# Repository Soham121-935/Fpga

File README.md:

# SV-16 Rev B — 16-Bit Microcontroller on a Lattice ECP5

SV-16 is a complete 16-bit microcontroller system in synthesizable
SystemVerilog for the **Lattice ECP5 `LFE5U-12F-6TG144C`**. It is not just a
CPU: it boots from SPI flash by itself, runs applications out of on-chip SRAM,
and can be reprogrammed over a plain serial port.

```
        ┌──────────────────────── LFE5U-12F-6TG144C ─────────────────────────┐
 25 MHz │  boot ROM (monitor)          SRAM 32 KB          MMIO 16 blocks    │
 ──────►│  ┌────────────┐   ┌──────────────────────┐  ┌──────────────────┐   │
        │  │ SV-16 CPU  │──►│ bus interconnect     │─►│ GPIO A/B, timer, │   │
 reset ─►│  │ 8 regs,    │   │ held req / qual ack  │  │ PWM+fault, UART, │   │
        │  │ 16-bit ALU │   │ held grant, 2 masters│  │ SPI, flash ctrl, │   │
        │  └────────────┘   └──────────────────────┘  │ IRQ, boot, system│   │
        │                                  watchdog ──►│  WDT, GPIO, SPI  │   │
        │      ▲ boot loader (hardware) ─────────────────────────────────►   │
        └──────┼───────────────────────────────────────────────┬──────────┘
               │  streams + CRC-checks the image from flash    │ 4 SPI pins
        ┌──────┴──────────────────────────┐            ┌───────┴─────────┐
        │  SPI NOR flash — the firmware   │            │ UART console /  │
        │  (survives power cycles)        │            │ upload 115200   │
        └─────────────────────────────────┘            └─────────────────┘
```

## Quick start

```sh
source scripts/sv16_venv.sh    # fetches Verilator + Yosys + nextpnr + ecppack
make test                      # lint + 18 simulation suites (473 checks)
make bitstream                 # -> build/sv16_top.bit (boot ROM baked in)
make prog                      # openFPGALoader over JTAG
make release                   # verify all four artifacts + hashes (run before programming)
make app                       # build the example application image
make upload PORT=/dev/ttyUSB0  # erase + upload + verify over UART
make upload-slot SLOT=1        # field update: install into the inactive slot
make mon-boot && make commit   # boot it (trial starts), then commit it
```

A fresh board comes up as a monitor on the serial port at **115200 8-N-1**:

```
SV-16 monitor v1
> ?
  C<addr4><len4><crc4>  program flash (hex payload follows)
  R<addr4><len4>        read flash
  E<addr4>              erase 4 KB sector
  V<addr4>              CRC16 of the image at addr
  B                     verify and boot the image at 0
  ?                     this help
+
```

## What it can do

* **16-bit CPU** — 8 general-purpose registers, `LDI/JMP/CALL` 2-word forms,
  ALU with multiply/divide/shift, Z/C/N/V flags, interrupt-enable flag, trap on
  illegal opcodes ([ISA.md](docs/ISA.md)).
* **32 KB SRAM, 4 KB boot ROM, 16 MMIO blocks** — a documented map with no
  decode holes that can hang the bus ([MEMORY_MAP.md](docs/MEMORY_MAP.md)).
* **Peripherals** — two 16-bit GPIO ports with atomic set/clear, timer, PWM with
  a hardware motor-fault input, UART with FIFOs, SPI master, a full SPI-NOR flash
  controller (read/program/erase/CRC), interrupt controller with priority and an
  8-entry vector table, and a **windowed, key-protected watchdog** that restarts
  the SoC if the application hangs ([PERIPHERALS.md](docs/PERIPHERALS.md#watchdog-0xf080)).
* **Real boot flow** — power-on → hardware loader validates and copies the flash
  image → CPU released at the application's entry point with the application's
  stack pointer; any failure falls back to the resident monitor
  ([BOOT_AND_PROGRAMMING.md](docs/BOOT_AND_PROGRAMMING.md)).
* **Field updates over UART** — CRC-checked images, per-byte acknowledgement,
  hex protocol a human can type, or `make upload` with `scripts/sv16_mon.py`.
* **Recoverable by design** — the monitor and the loader are in the FPGA
  configuration, so a broken application cannot brick the board; reset causes,
  fault addresses and a CPU state snapshot are all readable registers. A hung
  application is restarted by the watchdog, which the application cannot disarm
  and which re-arms itself after every bite.

## Build targets

| Command | Result |
| :--- | :--- |
| `make test` | lint + all eighteen Verilator suites (473 checks) |
| `make pcb` | the whole board starter kit: KiCad schematic and board file, six bitmaps, BOM/CPL, `FAB_NOTES.md`, `PCB_CONNECTIONS.md` |
| `make pcb-check` | parse the generated schematic and board back and re-verify them (nets, pads, DRC-lite, placement) |
| `make app` | build the example application image |
| `make bitstream` | `build/sv16_top.bit` for the LFE5U-12F-6TG144C, timing PASS at 25 MHz |
| `make synth` | Yosys only (fast synthesizability check) |
| `make prog` | program the FPGA over JTAG |
| `make release` | build the bitstream and the A/B image, then verify every artifact (ROM matches its source, timing, device budget, image CRCs, slot record) and write `build/release/` with hashes and the programming sequence |
| `make upload PORT=...` | program the *firmware* over the serial port |
| `make upload-slot SLOT=1` | field update into the inactive A/B slot (ADR-019) |
| `make commit` | commit a trial image (monitor `K`) |
| `make iss` | instruction-set simulator on the legacy ROM image |

Clocking: `CLKSRC=osc` (default) runs the SoC straight from the 25 MHz oscillator
— no PLL, no fabric divider — with ~75 % timing margin (measured Fmax 43.7 MHz);
`make bitstream CLKSRC=pll PLLMHZ=37.5` builds a **37.5 MHz** version from the
on-chip PLL (ADR-021), and `CLKDIV=2` halves whichever source is selected. The
UART divisor is derived from the built clock automatically (217 at 25 MHz, 326 at
37.5 MHz), so the console is always 115200 and firmware does not care.

## Repository layout

```text
BOARD.md/.pdf    PCB blueprint: components, specs, power tree, connection diagram
TEAM_PLAN.md/.pdf 4-person build plan: roles, phases, work packages, gates, budget, risks
hardware/       KiCad schematic (sv16_board.kicad_sch) + board base (footprints + netlist
                + rail pours + escape vias, ready to route)
                + six board bitmaps (top, bottom, net map, power map, connection sheets, schematic)
                + BOM.csv, JLCPCB_BOM.csv, JLCPCB_CPL.csv, FAB_NOTES.md (ordering and assembly)
                + cart/ (the parts you actually bought, reconciled against footprints)
PCB_CONNECTIONS.md/.pdf  the wiring: every pad, every net, every connector pinout, drawn
KICAD_TUTORIAL.md/.pdf  the click-by-click guide to finishing that board in KiCad
board/           device pin database + generated 144-pin net table (BOARD.md appendix)
docs/            operator manual, memory map, peripherals, flow, verification, ADRs
rtl/             26 SystemVerilog files: CPU, bus, memory, peripherals, PLL, SoC top
simulation/      Verilator testbenches (unit + regression) and the SPI flash model
firmware/        monitor assembler source, examples, drivers header, image packer
constraints/     ecp5_144tqfp.lpf — verified pin map for the TQFP-144 part
scripts/         assembler, image packer, RTL lint, TB runner, host programmer, toolchain
build/           generated: ROM image, firmware images, netlist, bitstream (untracked)
```

## Status, honestly

| | |
| :--- | :--- |
| Simulation | 473 checks, 0 failures across 18 suites (CPU/ISA, control instructions, interrupt latency, ALU/divider, RAM, timer, PWM, GPIO, UART, watchdog, flash controller, boot loader, A/B slots, PLL clock, monitor) |
| Synthesis / P&R | places, routes, packs for the target part; 77 % of the datasheet's LUT budget, 56 % of its block RAM (checked by the build, ADR-025) |
| Timing | 44.70 MHz Fmax measured at 25 MHz (~79 % margin); 45.45 MHz at `CLKSRC=pll PLLMHZ=37.5` (~21 % margin) |
| Silicon | **never run on hardware** — simulation and static timing only |

What is still missing for a production-grade MCU (JTAG debug, image signing,
a C toolchain, silicon bring-up) is
listed with reasoning in
**[docs/MCU_READINESS.md](docs/MCU_READINESS.md)** — including an explicit
MCU-like vs. FPGA-soft-core comparison.

## Documentation

| Document | Contents |
| :--- | :--- |
| [PCB_CONNECTIONS.pdf](PCB_CONNECTIONS.pdf) | **start here if you are the one wiring or routing it**: every pad of every part and what it connects to, connector pinouts, the power tree, the six connection sheets drawn, what the generator already connected, and the twelve checks before routing (source: [PCB_CONNECTIONS.md](PCB_CONNECTIONS.md), rebuild with `make pcb-connections-pdf`) |
| [KICAD_TUTORIAL.pdf](KICAD_TUTORIAL.pdf) | **start here if you are the one routing the board**: opening the project, updating the footprints, the design rules, filling and splitting the planes, the routing order with exact widths, DRC, gerbers, ordering, assembly and first power-up (source: [KICAD_TUTORIAL.md](KICAD_TUTORIAL.md), rebuild with `make tutorial-pdf`) |
| [TEAM_PLAN.pdf](TEAM_PLAN.pdf) | how to build this with four people: roles, five phases, gates, 16 work packages, interfaces to freeze, budget, risks (source: [TEAM_PLAN.md](TEAM_PLAN.md), rebuild with `make plan-pdf`) |
| [BOARD.pdf](BOARD.pdf) | the same blueprint typeset for printing / review (source: [BOARD.md](BOARD.md), rebuild with `make board-pdf`) |
| [BOARD.md](BOARD.md) | PCB blueprint — BOM with part numbers, power tree, pin map, connection circuit diagram, bring-up plan, open items |
| [board/TQFP144_PINOUT.md](board/TQFP144_PINOUT.md) | generated 144-pin device table: pad, bank, rail, design signal, board net |
| [BOOT_AND_PROGRAMMING.md](docs/BOOT_AND_PROGRAMMING.md) | boot flow, monitor protocol, image format, host tools, recovery |
| [MCU_READINESS.md](docs/MCU_READINESS.md) | what is MCU-like, what is still soft-core, gap list |
| [SYNTHESIS_AND_DEPLOYMENT.md](docs/SYNTHESIS_AND_DEPLOYMENT.md) | toolchain, build targets, utilisation, timing, pin map, programming |
| [MEMORY_MAP.md](docs/MEMORY_MAP.md) | address map, MMIO blocks, vector table |
| [PERIPHERALS.md](docs/PERIPHERALS.md) | register reference for every block |
| [BUS_ARCHITECTURE.md](docs/BUS_ARCHITECTURE.md) | protocol, arbitration, timing, adding a peripheral |
| [VERIFICATION.md](docs/VERIFICATION.md) | what is tested, what is not, bugs found |
| [RESET_AND_CLOCK.md](docs/RESET_AND_CLOCK.md) | clocking, reset sources, startup FSM |
| [ISA.md](docs/ISA.md) | instruction set, encodings, Rev B notes |
| [ARCHITECTURE_DECISIONS.md](docs/ARCHITECTURE_DECISIONS.md) | ADR-001..005 (Rev A), ADR-012..016 (Rev B) |

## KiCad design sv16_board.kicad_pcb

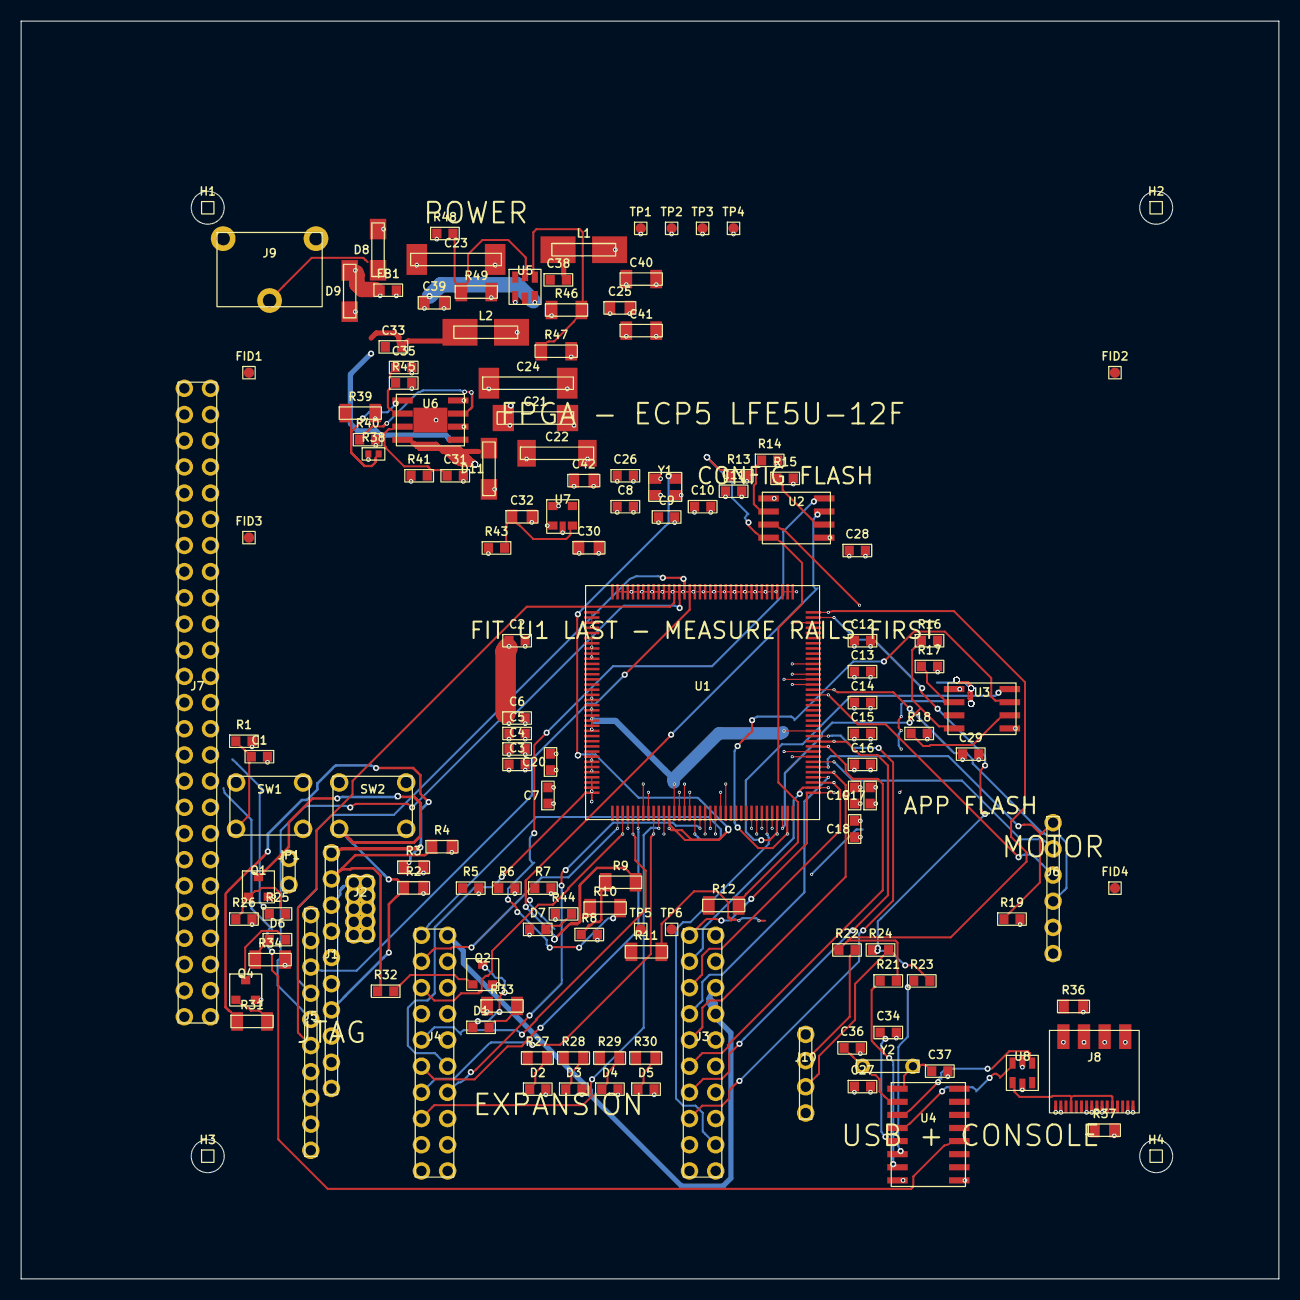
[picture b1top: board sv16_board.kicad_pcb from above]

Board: 4 copper layers, 122.0 x 122.0 mm, 141 parts (0 on the bottom side), 118 nets.

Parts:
C1, C2, C3, C4, C5, C6, C7, C8, C9, C10, C11, C12, C13, C14, C15, C16, C17, C18, C19, C20, C26, C27, C28, C29, C33, C34, C35, C36, C37, C38: 100nF; C_0603_1608Metric
C21: 100uF 25V tant; CP_EIA-7343-31_Kemet-D
C22: 22uF 63V; CP_Elec_6.3x5.4
C23: 470uF 25V; CP_Elec_8x10.5
C24: 220uF 16V; CP_Elec_8x10.5
C25, C30, C39, C42: 10uF; C_0805_2012Metric
C31: 470nF; C_0603_1608Metric
C32: 470nF; C_0805_2012Metric
C40, C41: 22uF; C_1206_3216Metric
D1, D2, D3, D4, D5: LED green; LED_0603_1608Metric
D6, D7: LED red; LED_0603_1608Metric
D8, D9, D11: SS34; D_SMA
FB1: 600R @100MHz; L_0603_1608Metric
FID1: FID1; Fiducial_1mm_Mask2mm
FID2: FID2; Fiducial_1mm_Mask2mm
FID3: FID3; Fiducial_1mm_Mask2mm
FID4: FID4; Fiducial_1mm_Mask2mm
H1: H1; MountingHole_3.2mm_M3
H2: H2; MountingHole_3.2mm_M3
H3: H3; MountingHole_3.2mm_M3
H4: H4; MountingHole_3.2mm_M3
J1: JTAG; PinHeader_1x10_P2.54mm_Vertical
J2: JTAG-1.27; PinHeader_2x05_P1.27mm_Vertical
J3: EXP-A; PinHeader_2x10_P2.54mm_Vertical
J4: EXP-B; PinHeader_2x10_P2.54mm_Vertical
J5: EXP-C; PinHeader_1x10_P2.54mm_Vertical
J6: MOTOR; PinHeader_1x06_P2.54mm_Vertical
J7: SPARE (not fitted); PinHeader_2x25_P2.54mm_Vertical
J8: USB-C; USB_C_Receptacle_HRO_TYPE-C-31-M-12
J9: 7-12 V; BarrelJack_CUI_PJ-102AH_Horizontal
J10: CONSOLE; PinHeader_1x04_P2.54mm_Vertical
JP1: DTR ENABLE; PinHeader_1x02_P2.54mm_Vertical
L1, L2: 10 uH; L_Sunlord_MWSA0518_5.4x5.2mm
Q1: 2N7002; SOT-23
Q2: BC817; SOT-23
Q4: BC807; SOT-23
R1: R1; R_0603_1608Metric
R2: R2; R_0805_2012Metric
R3: R3; R_0805_2012Metric
R4: R4; R_0805_2012Metric
R5: R5; R_0603_1608Metric
R6: R6; R_0603_1608Metric
R7: R7; R_0603_1608Metric
R8: R8; R_0603_1608Metric
R9: R9; R_1206_3216Metric
R10: R10; R_1206_3216Metric
R11: R11; R_1206_3216Metric
R12: R12; R_1206_3216Metric
R13: R13; R_0603_1608Metric
R14: R14; R_0603_1608Metric
R15: R15; R_0603_1608Metric
R16: R16; R_0603_1608Metric
R17: R17; R_0603_1608Metric
R18: R18; R_0603_1608Metric
R19: R19; R_0603_1608Metric
R21: R21; R_0603_1608Metric
R22: R22; R_0603_1608Metric
R23: R23; R_0603_1608Metric
R24: R24; R_0603_1608Metric
R25: R25; R_0603_1608Metric
R26: R26; R_0603_1608Metric
R27: R27; R_0805_2012Metric
R28: R28; R_0805_2012Metric
R29: R29; R_0805_2012Metric
R30: R30; R_0805_2012Metric
R31: R31; R_1206_3216Metric
R32: R32; R_0603_1608Metric
R33: R33; R_1206_3216Metric
R34: R34; R_1206_3216Metric
R36, R37: 5.1k; R_0805_2012Metric
R38: 12.4k; R_0402_1005Metric
R39, R46, R49: 33k; R_1206_3216Metric
R40, R41, R43, R48: 100k; R_0603_1608Metric
R44: R44; R_0603_1608Metric
R45: 10k; R_0603_1608Metric
R47: 10k; R_1206_3216Metric
SW1: RESET; SW_PUSH_6mm
SW2: RECONFIG; SW_PUSH_6mm
TP1: 3V3; TestPoint_Pad_D1.0mm
TP2: 2V5; TestPoint_Pad_D1.0mm
TP3: 1V1; TestPoint_Pad_D1.0mm
TP4: GND; TestPoint_Pad_D1.0mm
TP5: DONE; TestPoint_Pad_D1.0mm
TP6: INITN; TestPoint_Pad_D1.0mm
U1: LFE5U-12F-6TG144C; LQFP-144_20x20mm_P0.5mm
U2, U3: W25Q64JVSSIQ; SOIC-8_5.23x5.23mm_P1.27mm
U4: CH340G; SOIC-16_3.9x9.9mm_P1.27mm
U5: AP62300TWU-7; SOT-23-6
U6: MP1584EN; SOIC-8-1EP_3.9x4.9mm_P1.27mm_EP2.41x3.3mm
U7: LP5907MFX-2.5; SOT-23-5
U8: USBLC6-2SC6; SOT-23-6
Y1: 25 MHz ACTIVE XO (4-pin); Oscillator_SMD_Abracon_ASE-4Pin_3.2x2.5mm
Y2: 12 MHz (CH340G clock); Crystal_HC49-4H_Vertical

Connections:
1V1: C2.1, C3.1, C4.1, C5.1, C6.1, C7.1, C21.1, L2.2, R38.1, TP3.1, U1.20, U1.29, U1.38, U1.66, U1.83, U1.130
2V5: C8.1, C9.1, C10.1, C11.1, C22.1, C42.1, TP2.1, U1.17, U1.53, U1.96, U1.132, U7.5
3V3: C12.1, C13.1, C14.1, C15.1, C16.1, C17.1, C18.1, C19.1, C20.1, C24.1, C25.1, C26.1, C27.1, C28.1, C29.1, C30.1, C40.1, C41.1, D2.2, D3.2, D4.2, D5.2, J1.1, J2.1, J3.1, J4.1, J5.10, J10.1, L1.2, Q4.2, R1.2, R2.2, R3.2, R4.2, R5.2, R8.2, R13.2, R14.2, R15.2, R16.2, R17.2, R18.2, R19.2, R33.1, R43.1, R44.1, R46.1, TP1.1, U1.9, U1.16, U1.36, U1.43, U1.70, U1.86, U1.100, U1.122, U1.137, U2.8, U3.8, U4.16, U7.1, Y1.1, Y1.4
5V_USB: J3.17, J3.18, J4.20
A0: J5.1, U1.45
A1: J5.2, R11.1, U1.46
A2: J5.3, R10.1, U1.47
A3: J5.4, U1.48
A4: J5.5, R12.1, U1.49
A5: J5.6, U1.50
A6: J5.7, U1.51
A7: J5.8, U1.52
A8: J3.3, U1.97
A9: J3.4, U1.98
A10: J3.5, U1.99
A11: J3.6, U1.104
A12: J3.7, U1.105
A13: J3.8, U1.106
A14: J3.9, U1.107
A15: J3.10, U1.108
B0: J4.3, U1.135
B1: J4.4, U1.136
B2: J4.5, U1.139
B3: J4.6, U1.140
B4: J4.7, U1.141
B5: J4.8, U1.142
B6: J4.9, U1.143
B7: J4.10, U1.128
B8: J4.11, U1.124
B9: J4.12, U1.125
B10: J4.13, U1.126
B11: J4.14, U1.127
B12: J4.15, U1.1
B13: J4.16, U1.2
B14: J4.17, U1.3
B15: J4.18, U1.4
CC1: J8.A5, R36.1
CC2: J8.B5, R37.1
CCLK: R8.1, R9.1, U1.54
CFG_0: R6.1, U1.62
CFG_1: R5.1, U1.59
CFG_2: R7.1, U1.58
D1_A: D1.2, R33.2
D6_K: D6.1, R34.1
D7_A: D7.2, R44.2
DONE: J1.9, R4.1, R32.1, TP5.1, U1.56
DTR_F: JP1.2, R25.1
FB_1V1: R38.2, R39.1, U6.4
GND: C1.2, C2.2, C3.2, C4.2, C5.2, C6.2, C7.2, C8.2, C9.2, C10.2, C11.2, C12.2, C13.2, C14.2, C15.2, C16.2, C17.2, C18.2, C19.2, C20.2, C21.2, C22.2, C23.2, C24.2, C25.2, C26.2, C27.2, C28.2, C29.2, C30.2, C31.2, C32.2, C34.2, C35.2, C36.2, C37.2, C39.2, C40.2, C41.2, C42.2, D7.1, D11.2, J1.7, J2.6, J2.10, J3.2, J3.15, J3.16, J3.19, J3.20, J4.2, J4.19, J5.9, J6.2, J8.A1, J8.A12, J8.B1, J8.B12, J8.S1, J8.S2, J8.S3, J8.S4, J9.2, J10.4, Q1.2, Q2.2, R6.2, R7.2, R26.2, R34.2, R36.2, R37.2, R39.2, R40.2, R45.2, R47.2, R49.2, SW1.2, SW2.2, TP4.1, U1.8, U1.15, U1.21, U1.32, U1.42, U1.65, U1.75, U1.85, U1.87, U1.101, U1.123, U1.129, U1.131, U1.138, U2.4, U3.4, U4.1, U5.1, U6.5, U6.9, U7.2, U8.2, Y1.2
INITN: J1.10, R3.1, R31.1, TP6.1, U1.55
J9_VIN: D8.2, J9.1
J10_RX: J10.3, R22.2
J10_TX: J10.2, R24.2
PROGRAMN: J1.4, Q1.3, R2.1, SW2.1, U1.57
Q1_G: Q1.1, R25.2, R26.1
Q2_B: Q2.1, R32.2
Q2_C: D1.1, Q2.3
Q4_B: Q4.1, R31.2
Q4_C: D6.2, Q4.3
TCK: J1.8, J2.5, U1.63
TDI: J1.3, J2.3, U1.61
TDO: J1.2, J2.4, U1.60
TMS: J1.6, J2.2, U1.64
U2_CLK: R9.2, U2.6
U2_CS: R12.2, R13.1, U2.1
U2_DI: R10.2, U2.5
U2_DO: R11.2, U2.2
U2_HOLD: R15.1, U2.7
U2_WP: R14.1, U2.3
U3_HOLD: R18.1, U3.7
U3_WP: R17.1, U3.3
U4_DTR: JP1.1, U4.13
U4_RXD: R23.1, U4.3
U4_TXD: R21.1, U4.2
U4_V3: C34.1, U4.4
U5_BST: C38.1, U5.6
U5_EN: R48.2, R49.1, U5.5
U5_FB: R46.2, R47.1, U5.4
U5_SW: C38.2, L1.1, U5.2
U6_BST: C33.1, U6.8
U6_COMP: C35.1, R45.1, U6.3
U6_EN: C31.1, R41.2, U6.2
U6_FREQ: R40.1, U6.6
U6_SW: C33.2, D11.1, L2.1, U6.1
U7_EN: C32.1, R43.2, U7.3
USB_DN: J8.A7, J8.B7, U8.3
USB_DN_F: U4.6, U8.4
USB_DP: J8.A6, J8.B6, U8.1
USB_DP_F: U4.5, U8.6
USB_VBUS: D9.2, J8.A4, J8.A9, J8.B4, J8.B9, U8.5
VM_IN: C23.1, C39.1, FB1.2, J6.1, R41.1, R48.1, U5.3, U6.7
VM_IN_RAW: D8.1, D9.1, FB1.1
Y2_XI: C36.1, U4.7, Y2.1
Y2_XO: C37.1, U4.8, Y2.2
clk_25m: U1.133, Y1.3
ext_rst_n: C1.1, R1.1, SW1.1, U1.134
flash_cs_n: R16.1, U1.111, U3.1
flash_miso: U1.113, U3.2
flash_mosi: U1.112, U3.5
flash_sck: U1.110, U3.6
led0: R27.1, U1.39
led0_k: D2.1, R27.2
led1: R28.1, U1.40
led1_k: D3.1, R28.2
led2: R29.1, U1.41
led2_k: D4.1, R29.2
led3: R30.1, U1.44
led3_k: D5.1, R30.2
motor_dir1: J6.4, U1.89
motor_dir2: J6.5, U1.102
motor_fault_n: J6.6, R19.1, U1.103
pwm_out: J6.3, U1.88
spi0_cs_n: J3.11, U1.115
spi0_miso: J3.14, U1.117
spi0_mosi: J3.13, U1.116
spi0_sck: J3.12, U1.114
uart_rx: R21.2, R22.1, U1.73
uart_tx: R23.2, R24.1, U1.74

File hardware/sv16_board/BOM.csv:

Quantity,Value,Footprint,References,Part number,DNP,Notes
1,7-12 V,BarrelJack_CUI_PJ-102AH_Horizontal,J9,,,
1,100uF 25V tant,CP_EIA-7343-31_Kemet-D,C21,"100 uF 25 V tantalum, D case",,1V1 bulk; mind the polarity bar
1,22uF 63V,CP_Elec_6.3x5.4,C22,22 uF 63 V electrolytic,,D6.3 x L5.4 mm
1,220uF 16V,CP_Elec_8x10.5,C24,220 uF hybrid electrolytic,,D8 x L10.5 mm; hybrid polymer is better for ripple
1,470uF 25V,CP_Elec_8x10.5,C23,470 uF 25 V (35 V preferred),,the cart part is 16 V - on a 12 V rail that is only 1.33x derating
30,100nF,C_0603_1608Metric,C1 C2 C3 C4 C5 C6 C7 C8 C9 C10 C11 C12 C13 C14 C15 C16 C17 C18 C19 C20 C26 C27 C28 C29 C33 C34 C35 C36 C37 C38,,,
1,470nF,C_0603_1608Metric,C31,,,
4,10uF,C_0805_2012Metric,C25 C30 C39 C42,10 uF,,TO BUY - 3V3 bulk near the FPGA banks
1,470nF,C_0805_2012Metric,C32,,,
2,22uF,C_1206_3216Metric,C40 C41,22 uF X5R 25 V,,TO BUY - 3V3 output ceramic
1,12 MHz (CH340G clock),Crystal_HC49-4H_Vertical,Y2,12 MHz crystal,,"CH340G clock; CL 12-20 pF, choose C36/C37 to match"
3,SS34,D_SMA,D8 D9 D11,SS34,,SMA; input ORing
4,,Fiducial_1mm_Mask2mm,FID1 FID2 FID3 FID4,,,
5,LED green,LED_0603_1608Metric,D1 D2 D3 D4 D5,,,
1,LED red,LED_0603_1608Metric,D6,,yes,
1,LED red,LED_0603_1608Metric,D7,,,
1,LFE5U-12F-6TG144C,LQFP-144_20x20mm_P0.5mm,U1,LFE5U-12F-6TG144C,,no substitute; order a spare (BOARD.md 3.4)
1,600R @100MHz,L_0603_1608Metric,FB1,600 ohm @ 100 MHz ferrite,,"0603, >= 500 mA"
2,10 uH,L_Sunlord_MWSA0518_5.4x5.2mm,L1 L2,CD54 10 uH >= 1.5 A,,AP62300 3V3 inductor; the cart has 2 x 33 uH as spares
4,,MountingHole_3.2mm_M3,H1 H2 H3 H4,,,
1,25 MHz ACTIVE XO (4-pin),Oscillator_SMD_Abracon_ASE-4Pin_3.2x2.5mm,Y1,YIC OSC25M-3.3I/S3-25T,,"ACTIVE 25 MHz 3.3 V XO, 4-pin - a 2-pin crystal will not clock the FPGA"
1,DTR ENABLE,PinHeader_1x02_P2.54mm_Vertical,JP1,,,
1,CONSOLE,PinHeader_1x04_P2.54mm_Vertical,J10,,,
1,MOTOR,PinHeader_1x06_P2.54mm_Vertical,J6,,,
1,EXP-C,PinHeader_1x10_P2.54mm_Vertical,J5,,,
1,JTAG,PinHeader_1x10_P2.54mm_Vertical,J1,,,
1,JTAG-1.27,PinHeader_2x05_P1.27mm_Vertical,J2,,,
1,EXP-A,PinHeader_2x10_P2.54mm_Vertical,J3,,,
1,EXP-B,PinHeader_2x10_P2.54mm_Vertical,J4,,,
1,SPARE (not fitted),PinHeader_2x25_P2.54mm_Vertical,J7,,yes,
1,12.4k,R_0402_1005Metric,R38,,,
14,,R_0603_1608Metric,R1 R5 R6 R7 R8 R13 R14 R15 R16 R17 R18 R25 R26 R32,,,
3,0R,R_0603_1608Metric,R21 R23 R44,,,
2,0R (or not fitted),R_0603_1608Metric,R22 R24,,,
4,100k,R_0603_1608Metric,R40 R41 R43 R48,,,
2,10k,R_0603_1608Metric,R19 R45,,,
7,,R_0805_2012Metric,R2 R3 R4 R27 R28 R29 R30,,,
2,5.1k,R_0805_2012Metric,R36 R37,,,
7,,R_1206_3216Metric,R9 R10 R11 R12 R31 R33 R34,,,
1,10k,R_1206_3216Metric,R47,10 kohm 1 %,,TO BUY - AP62300 feedback bottom leg
3,33k,R_1206_3216Metric,R39 R46 R49,,,
1,CH340G,SOIC-16_3.9x9.9mm_P1.27mm,U4,CH340G,,SOP-16; needs Y2 12 MHz + C36/C37 (the C variant does not)
1,MP1584EN,SOIC-8-1EP_3.9x4.9mm_P1.27mm_EP2.41x3.3mm,U6,MP1584EN-LF-Z,,SOIC-8E; solder the exposed pad (thermal vias are placed)
2,W25Q64JVSSIQ,SOIC-8_5.23x5.23mm_P1.27mm,U2 U3,W25Q64JVSSIQ,,bitstream flash
1,2N7002,SOT-23,Q1,2N7002,,"SOT-23, PROGRAMN pull-down from DTR"
1,BC807,SOT-23,Q4,MMBT3906 (cart) / BC807,,INITN indicator
1,BC817,SOT-23,Q2,MMBT3904 (cart) / BC817,,DONE indicator
1,LP5907MFX-2.5,SOT-23-5,U7,LP5907MFX-2.5,,SOT-23-5; needs a low-ESR 10 uF on OUT (C42)
1,AP62300TWU-7,SOT-23-6,U5,AP62300TWU-7,,TSOT-26; EN is a 6 V pin - use the R48/R49 divider
1,USBLC6-2SC6,SOT-23-6,U8,USBLC6-2SC6,,"SOT-23-6, place at the connector"
1,RECONFIG,SW_PUSH_6mm,SW2,,,
1,RESET,SW_PUSH_6mm,SW1,,,
1,1V1,TestPoint_Pad_D1.0mm,TP3,,,
1,2V5,TestPoint_Pad_D1.0mm,TP2,,,
1,3V3,TestPoint_Pad_D1.0mm,TP1,,,
1,DONE,TestPoint_Pad_D1.0mm,TP5,,,
1,GND,TestPoint_Pad_D1.0mm,TP4,,,
1,INITN,TestPoint_Pad_D1.0mm,TP6,,,
1,USB-C,USB_C_Receptacle_HRO_TYPE-C-31-M-12,J8,,,

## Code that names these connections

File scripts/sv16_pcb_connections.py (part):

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    "VM_IN_RAW": "barrel / USB ORing node before FB1",
    "USB_VBUS": "5 V from the USB-C connector",
    "5V_USB": "VBUS only - J3/J4 pins 17/18/20, do not power the board here",
    "CCLK": "FPGA configuration clock (pin 54), R8 pull-up, R9 to U2",
    "U2_CLK": "U2 clock after the 100 ohm damping resistor",
    "MOSI": "FPGA configuration data out (pin 47)", "U2_DI": "U2 data in",
    "MISO": "FPGA configuration data in (pin 46)", "U2_DO": "U2 data out",
    "CSSPIN": "FPGA configuration chip select (pin 49)", "U2_CS": "U2 chip select",
    "U2_WP": "U2 write protect (pulled high)", "U2_HOLD": "U2 hold (pulled high)",
    "PROGRAMN": "configuration trigger, active low", "INITN": "SRAM clear / config error",
    "DONE": "configuration complete, high when running",
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    "DTR": "CH340G DTR# output", "DTR_F": "DTR after the JP1 jumper",
    "Q2_B": "Q2 base", "Q2_C": "Q2 collector", "DONE_LED": "D1 anode",
    "Q4_B": "Q4 base", "Q4_C": "Q4 collector", "INITN_LED": "D6 cathode side",
    "clk_25m": "the 25 MHz clock into U1 pin 133",
    "uart_rx": "into the SoC (FPGA pin 73), idles high",
    "uart_tx": "out of the SoC (FPGA pin 74)",
    "U4_TXD": "CH340G transmit out", "U4_RXD": "CH340G receive in",
    "flash_sck": "application flash clock", "flash_cs_n": "application flash select",
    "flash_mosi": "application flash data out", "flash_miso": "application flash data in",
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    "USB_DP": "USB D+ at the connector", "USB_DN": "USB D- at the connector",
    "USB_DP_F": "USB D+ after the ESD device", "USB_DN_F": "USB D- after the ESD device",
    "CC1": "USB-C CC1, 5.1 k to GND", "CC2": "USB-C CC2, 5.1 k to GND",
    "U4_DTR": "CH340G DTR# pin 13", "U4_V3": "CH340G V3 pin, tied to 3V3",
    "Y2_XI": "12 MHz crystal, XI side", "Y2_XO": "12 MHz crystal, XO side",
    "U5_SW": "AP62300 switch node", "U5_BST": "AP62300 bootstrap",
    "U5_FB": "AP62300 feedback node", "U5_EN": "AP62300 enable (6 V pin)",
    "U6_SW": "MP1584 switch node", "U6_BST": "MP1584 bootstrap",
    "U6_EN": "MP1584 enable RC", "U6_FREQ": "MP1584 frequency set (900 kHz)",
    "FB_1V1": "1V1 feedback node", "U7_EN": "LP5907 enable RC", "U6_COMP": "MP1584 loop compensation",
    "U8_DP": "USBLC6 D+ (unused duplicate)", "U8_DN": "USBLC6 D- (unused duplicate)",
    "pwm_out": "motor PWM, 16 mA drive (pin 88)",
    "motor_dir1": "motor direction 1 (pin 89)", "motor_dir2": "motor direction 2 (pin 102)",
    "motor_fault_n": "motor fault input, pulled up (pin 103)",
    "spi0_sck": "SPI0 clock to EXP-A", "spi0_cs_n": "SPI0 chip select to EXP-A",
    "spi0_mosi": "SPI0 data out to EXP-A", "spi0_miso": "SPI0 data in to EXP-A",
    "J9_VIN": "barrel jack positive pin", "J10_TX": "console header TX side",
    "J10_RX": "console header RX side", "D7_A": "3V3-present LED anode",
    "D1_A": "D1 anode", "D6_K": "D6 cathode",
}
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| :-: | :--- | :--- | :--- |
| 1 | **The FPGA's rails** | 1V1 on pins 20/29/38/66/83/130, 2V5 on 17/53/96/132, 3V3 on 9/16/36/43/70/86/100/122/137. Getting one of these wrong is the classic dead-board bug | §4 |
| 2 | **The Master-SPI pads are also GPIOA pins** | `gpio_a[1]/[2]/[4]/[6]` share pins 46/47/49/51 with the configuration flash. Keep them **inputs** in firmware; R9–R12 (100 Ω) bound any contention | §4, §6 |
| 3 | **`EN` of the AP62300 is a 6 V pin** | never tie it to VM_IN — the R48/R49 divider is what protects it | §6 |
| 4 | **Y1 must be an active oscillator** | the ECP5 has no crystal driver; a 2-pin HC49/US part leaves the board with no clock, no console, no boot | §6 |
| 5 | **USB is a differential pair** | J8 → U8 → U4, no vias, gap 0.2 mm, length skew under 0.5 mm, CC resistors 5.1 k to GND | §4, §8 |

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  7  USB: the CH340G must appear as a serial port
  8  configure over J1 (openFPGALoader), then write the config flash
  9  DONE (TP5) high, monitor answers '?' at 115200 8-N-1
 10  DONE never rises -> scope clk_25m at Y1 pin 3, then check PROGRAMN, CCLK, U2
```
"""

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| 9 | Plug in USB | the CH340G appears as a serial port (`dmesg`, or Device Manager with the WCH driver) |
| 10 | Configure over J1 (`make prog`), then `make prog-flash` | DONE (TP5) goes high when the FPGA is configured |
| 11 | Open the console at 115200 8-N-1, send `?` | the monitor prints its help |
| 12 | If DONE never rises | scope `clk_25m` at Y1 pin 3 → then PROGRAMN (57), CCLK (54) and U2 |
"""

STILL_TO_BUY_SECTION = """
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
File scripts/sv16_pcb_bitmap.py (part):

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    "VM_IN_RAW": "#ff8c42", "5V_USB": "#ffb347", "USB_VBUS": "#ffb347",
    "clk_25m": "#ffd166",
    "CCLK": "#f4a261", "U2_CLK": "#f4a261", "MOSI": "#f4a261", "MISO": "#f4a261",
    "CSSPIN": "#f4a261", "U2_DI": "#f4a261", "U2_DO": "#f4a261", "U2_CS": "#f4a261",
    "PROGRAMN": "#e9c46a", "INITN": "#e9c46a", "DONE": "#e9c46a",
    "TCK": "#ffd60a", "TMS": "#ffd60a", "TDI": "#ffd60a", "TDO": "#ffd60a",
    "USB_DP": "#00b4d8", "USB_DN": "#00b4d8", "USB_DP_F": "#00b4d8",
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    block(x + 40, y + 450, 260, 130, "U1.56 DONE", "configured", "#e9c46a",
          "R4 4.7k to 3V3|J1.9|R32 -> Q2 -> D1")
    block(x + 40, y + 620, 260, 120, "mode straps", "latched at INITN rise", "#8b949e",
          "CFG_0 pin 62 -> R6 1k -> GND|CFG_1 pin 59 -> R5 4.7k -> 3V3|CFG_2 pin 58 -> R7 1k -> GND")
    block(x + 400, y + 110, 300, 200, "JTAG TAP", "always available", "#ffd60a",
          "TCK 63 -> J1.8 / J2.5|TMS 64 -> J1.6 / J2.2|TDI 61 -> J1.3 / J2.3|"
          "TDO 60 -> J1.2 / J2.4|GND J1.7 J2.6 J2.10")
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    block(x + 400, y + 510, 300, 130, "auto-reconfigure", "from the host", "#e9c46a",
          "U4 DTR# -> JP1 -> R25 4.7k -> Q1 gate|R26 10k gate to GND|bridge JP1 to enable")
    block(x + 770, y + 110, 340, 190, "reset", "SW1 + RC", "#f72585",
          "U1.134 ext_rst_n|SW1 to GND|R1 10k to 3V3|C1 100 nF to GND|pin has PULLMODE=UP too")
    block(x + 770, y + 330, 340, 190, "status LEDs", "all active low", "#84cc16",
          "led[0..3] pins 39 40 41 44|R27-R30 470R -> D2-D5 -> 3V3|"
          "D1 = DONE, D6 = INITN (DNP)|D7 = 3V3 present")
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          "TP1 3V3 (3.28 V)|TP2 2V5 (2.50 V)|TP3 1V1 (1.10 V)|TP4 GND|"
          "TP5 DONE (high = configured)|TP6 INITN (low = failure)")
    block(x + 400, y + 450, 330, 280, "motor interface", "J6", "#4cc9f0",
          "pwm_out   pin 88, 16 mA drive|motor_dir1 pin 89|motor_dir2 pin 102|"
          "motor_fault_n pin 103 + R19 10k|the fuse lives on the driver board|"
          "keep the motor return away from|the FPGA ground")
    block(x + 760, y + 450, 360, 280, "before you route", "BOARD.md 11", "#e9c46a",
          "Y1 within 10 mm of U1.133|U2 within 15 mm of pins 54/46/47/49|"
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        story_legend(canvas, [
            "TP1 3.28 V · TP3 1.10 V · TP2 2.50 V — measure with U1 NOT fitted, then again with it fitted",
            "current plan: 3V3 ~600 mA, 1V1 ~150 mA, 2V5 ~50 mA (BOARD.md 4.2); 0.8 mm traces, pours for the rest",
            "never tie U5 pin 5 (EN) to VM_IN: it is a 6 V pin - the R48/R49 divider is what protects it",
        ], "bench numbers")
        canvas.save(OUT / "pcb_power_map.png")

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
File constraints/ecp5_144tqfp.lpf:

# ---------------------------------------------------------------------------
# Lattice LPF constraints — SV-16 Rev B
# Device:  Lattice ECP5 LFE5U-12F-6TG144C (12K LUT, TQFP-144, speed grade 6)
#
# Every port of rtl/sv16_top.sv is located here, and every site below is a real
# IO site of this package (checked against the prjtrellis device database, and
# the whole design is placed and routed by `make bitstream`).  For TQFP packages
# the SITE name is the pin number, so pin 102 is written as "102".
#
# The pins marked "existing board wiring" come from the Rev A constraint file;
# the Rev A file also located clk P63, ext_rst_n P60, led[0] P38, pwm_out P100
# and motor_dir1 P101, none of which are IO sites on this package, so they
# could never have been placed.  They are re-assigned here.
#
# >>> BOARD WIRING: the pins that are not "existing board wiring" are a
# >>> documented, placeable default.  Change the SITE of a port to match your
# >>> board; nothing else in the design depends on the pin numbers.
#
# All ports are LVCMOS33, so every bank you use must have VCCIO = 3.3 V.
# ---------------------------------------------------------------------------

BLOCK RESETPATHS;
BLOCK ASYNCPATHS;

# --------------------------------------------------------------- clock / reset
# 25 MHz board oscillator.  This is the only clock in the design: the UART baud
# generator, timers, PWM and the SPI clock divider all derive from it, and the
# bus/interconnect logic is single-cycle at this clock.
LOCATE COMP "clk_25m" SITE "133";
IOBUF PORT "clk_25m" IO_TYPE=LVCMOS33;
FREQUENCY PORT "clk_25m" 25.000000 MHz;

# Active-low reset push button (also the hard reset of the MCU).
LOCATE COMP "ext_rst_n" SITE "134";
IOBUF PORT "ext_rst_n" IO_TYPE=LVCMOS33 PULLMODE=UP;

# ------------------------------------------- console UART (existing board wiring)
# The ROM monitor / bootloader console and the firmware upload interface.
LOCATE COMP "uart_rx" SITE "73";
IOBUF PORT "uart_rx" IO_TYPE=LVCMOS33 PULLMODE=UP;
LOCATE COMP "uart_tx" SITE "74";
IOBUF PORT "uart_tx" IO_TYPE=LVCMOS33;

# ---------------------------------------------- SPI configuration flash (program store)
# Persistent program storage: the monitor and the user images live here, and
# sv16_boot streams them into SRAM at power-on or on the B command.  If your
# board already has a configuration flash wired to the ECP5 CFG pins, either
# share that part bus (see docs/BOOT_AND_PROGRAMMING.md) or move these four
# ports onto the spare IO next to it.
LOCATE COMP "flash_sck"  SITE "110";
IOBUF PORT "flash_sck"  IO_TYPE=LVCMOS33 DRIVE=8;
LOCATE COMP "flash_cs_n" SITE "111";
IOBUF PORT "flash_cs_n" IO_TYPE=LVCMOS33 DRIVE=8;
LOCATE COMP "flash_mosi" SITE "112";
IOBUF PORT "flash_mosi" IO_TYPE=LVCMOS33 DRIVE=8;
LOCATE COMP "flash_miso" SITE "113";
IOBUF PORT "flash_miso" IO_TYPE=LVCMOS33 PULLMODE=UP;

# ------------------------------------------------------- SPI0 expansion bus (MMIO 0xF050)
LOCATE COMP "spi0_sck"  SITE "114";
IOBUF PORT "spi0_sck"  IO_TYPE=LVCMOS33 DRIVE=8;
LOCATE COMP "spi0_cs_n" SITE "115";
IOBUF PORT "spi0_cs_n" IO_TYPE=LVCMOS33 DRIVE=8;
LOCATE COMP "spi0_mosi" SITE "116";
IOBUF PORT "spi0_mosi" IO_TYPE=LVCMOS33 DRIVE=8;
LOCATE COMP "spi0_miso" SITE "117";
IOBUF PORT "spi0_miso" IO_TYPE=LVCMOS33 PULLMODE=UP;

# ------------------------------------------- status LEDs (active low, mirror GPIOA[3:0])
LOCATE COMP "led[0]" SITE "39";
IOBUF PORT "led[0]" IO_TYPE=LVCMOS33 DRIVE=8;
LOCATE COMP "led[1]" SITE "40";
IOBUF PORT "led[1]" IO_TYPE=LVCMOS33 DRIVE=8;
LOCATE COMP "led[2]" SITE "41";
IOBUF PORT "led[2]" IO_TYPE=LVCMOS33 DRIVE=8;
LOCATE COMP "led[3]" SITE "44";
IOBUF PORT "led[3]" IO_TYPE=LVCMOS33 DRIVE=8;

# ---------------------------------------------------- GPIO port A (MMIO 0xF010)
# 16-bit bidirectional port with per-pin direction (GPIO_DIR).  Bits 3:0 also
# drive the status LEDs, which is what the example firmware uses as heartbeat.
LOCATE COMP "gpio_a[0]"  SITE "45";
IOBUF PORT "gpio_a[0]"  IO_TYPE=LVCMOS33 DRIVE=8;
LOCATE COMP "gpio_a[1]"  SITE "46";
IOBUF PORT "gpio_a[1]"  IO_TYPE=LVCMOS33 DRIVE=8;
LOCATE COMP "gpio_a[2]"  SITE "47";
IOBUF PORT "gpio_a[2]"  IO_TYPE=LVCMOS33 DRIVE=8;
LOCATE COMP "gpio_a[3]"  SITE "48";
IOBUF PORT "gpio_a[3]"  IO_TYPE=LVCMOS33 DRIVE=8;
LOCATE COMP "gpio_a[4]"  SITE "49";
IOBUF PORT "gpio_a[4]"  IO_TYPE=LVCMOS33 DRIVE=8;
LOCATE COMP "gpio_a[5]"  SITE "50";
IOBUF PORT "gpio_a[5]"  IO_TYPE=LVCMOS33 DRIVE=8;
LOCATE COMP "gpio_a[6]"  SITE "51";
IOBUF PORT "gpio_a[6]"  IO_TYPE=LVCMOS33 DRIVE=8;
LOCATE COMP "gpio_a[7]"  SITE "52";
IOBUF PORT "gpio_a[7]"  IO_TYPE=LVCMOS33 DRIVE=8;
LOCATE COMP "gpio_a[8]"  SITE "97";
IOBUF PORT "gpio_a[8]"  IO_TYPE=LVCMOS33 DRIVE=8;
LOCATE COMP "gpio_a[9]"  SITE "98";
IOBUF PORT "gpio_a[9]"  IO_TYPE=LVCMOS33 DRIVE=8;
LOCATE COMP "gpio_a[10]" SITE "99";
IOBUF PORT "gpio_a[10]" IO_TYPE=LVCMOS33 DRIVE=8;
LOCATE COMP "gpio_a[11]" SITE "104";
IOBUF PORT "gpio_a[11]" IO_TYPE=LVCMOS33 DRIVE=8;
LOCATE COMP "gpio_a[12]" SITE "105";
IOBUF PORT "gpio_a[12]" IO_TYPE=LVCMOS33 DRIVE=8;
LOCATE COMP "gpio_a[13]" SITE "106";
IOBUF PORT "gpio_a[13]" IO_TYPE=LVCMOS33 DRIVE=8;
LOCATE COMP "gpio_a[14]" SITE "107";
IOBUF PORT "gpio_a[14]" IO_TYPE=LVCMOS33 DRIVE=8;
LOCATE COMP "gpio_a[15]" SITE "108";
IOBUF PORT "gpio_a[15]" IO_TYPE=LVCMOS33 DRIVE=8;

# ---------------------------------------------------- GPIO port B (MMIO 0xF070)
LOCATE COMP "gpio_b[0]"  SITE "135";
IOBUF PORT "gpio_b[0]"  IO_TYPE=LVCMOS33 DRIVE=8;
LOCATE COMP "gpio_b[1]"  SITE "136";
IOBUF PORT "gpio_b[1]"  IO_TYPE=LVCMOS33 DRIVE=8;
LOCATE COMP "gpio_b[2]"  SITE "139";
IOBUF PORT "gpio_b[2]"  IO_TYPE=LVCMOS33 DRIVE=8;
LOCATE COMP "gpio_b[3]"  SITE "140";
IOBUF PORT "gpio_b[3]"  IO_TYPE=LVCMOS33 DRIVE=8;
LOCATE COMP "gpio_b[4]"  SITE "141";
IOBUF PORT "gpio_b[4]"  IO_TYPE=LVCMOS33 DRIVE=8;
LOCATE COMP "gpio_b[5]"  SITE "142";
IOBUF PORT "gpio_b[5]"  IO_TYPE=LVCMOS33 DRIVE=8;
LOCATE COMP "gpio_b[6]"  SITE "143";
IOBUF PORT "gpio_b[6]"  IO_TYPE=LVCMOS33 DRIVE=8;
LOCATE COMP "gpio_b[7]"  SITE "128";
IOBUF PORT "gpio_b[7]"  IO_TYPE=LVCMOS33 DRIVE=8;
LOCATE COMP "gpio_b[8]"  SITE "124";
IOBUF PORT "gpio_b[8]"  IO_TYPE=LVCMOS33 DRIVE=8;
LOCATE COMP "gpio_b[9]"  SITE "125";
IOBUF PORT "gpio_b[9]"  IO_TYPE=LVCMOS33 DRIVE=8;
LOCATE COMP "gpio_b[10]" SITE "126";
IOBUF PORT "gpio_b[10]" IO_TYPE=LVCMOS33 DRIVE=8;
LOCATE COMP "gpio_b[11]" SITE "127";
IOBUF PORT "gpio_b[11]" IO_TYPE=LVCMOS33 DRIVE=8;
LOCATE COMP "gpio_b[12]" SITE "1";
IOBUF PORT "gpio_b[12]" IO_TYPE=LVCMOS33 DRIVE=8;
LOCATE COMP "gpio_b[13]" SITE "2";
IOBUF PORT "gpio_b[13]" IO_TYPE=LVCMOS33 DRIVE=8;
LOCATE COMP "gpio_b[14]" SITE "3";
IOBUF PORT "gpio_b[14]" IO_TYPE=LVCMOS33 DRIVE=8;
LOCATE COMP "gpio_b[15]" SITE "4";
IOBUF PORT "gpio_b[15]" IO_TYPE=LVCMOS33 DRIVE=8;

# ------------------------------------------- PWM / motor interface (MMIO 0xF030)
LOCATE COMP "pwm_out" SITE "88";
IOBUF PORT "pwm_out" IO_TYPE=LVCMOS33 DRIVE=16;
LOCATE COMP "motor_dir1" SITE "89";
IOBUF PORT "motor_dir1" IO_TYPE=LVCMOS33 DRIVE=8;
LOCATE COMP "motor_dir2" SITE "102";
IOBUF PORT "motor_dir2" IO_TYPE=LVCMOS33 DRIVE=8;
LOCATE COMP "motor_fault_n" SITE "103";
IOBUF PORT "motor_fault_n" IO_TYPE=LVCMOS33 PULLMODE=UP;
